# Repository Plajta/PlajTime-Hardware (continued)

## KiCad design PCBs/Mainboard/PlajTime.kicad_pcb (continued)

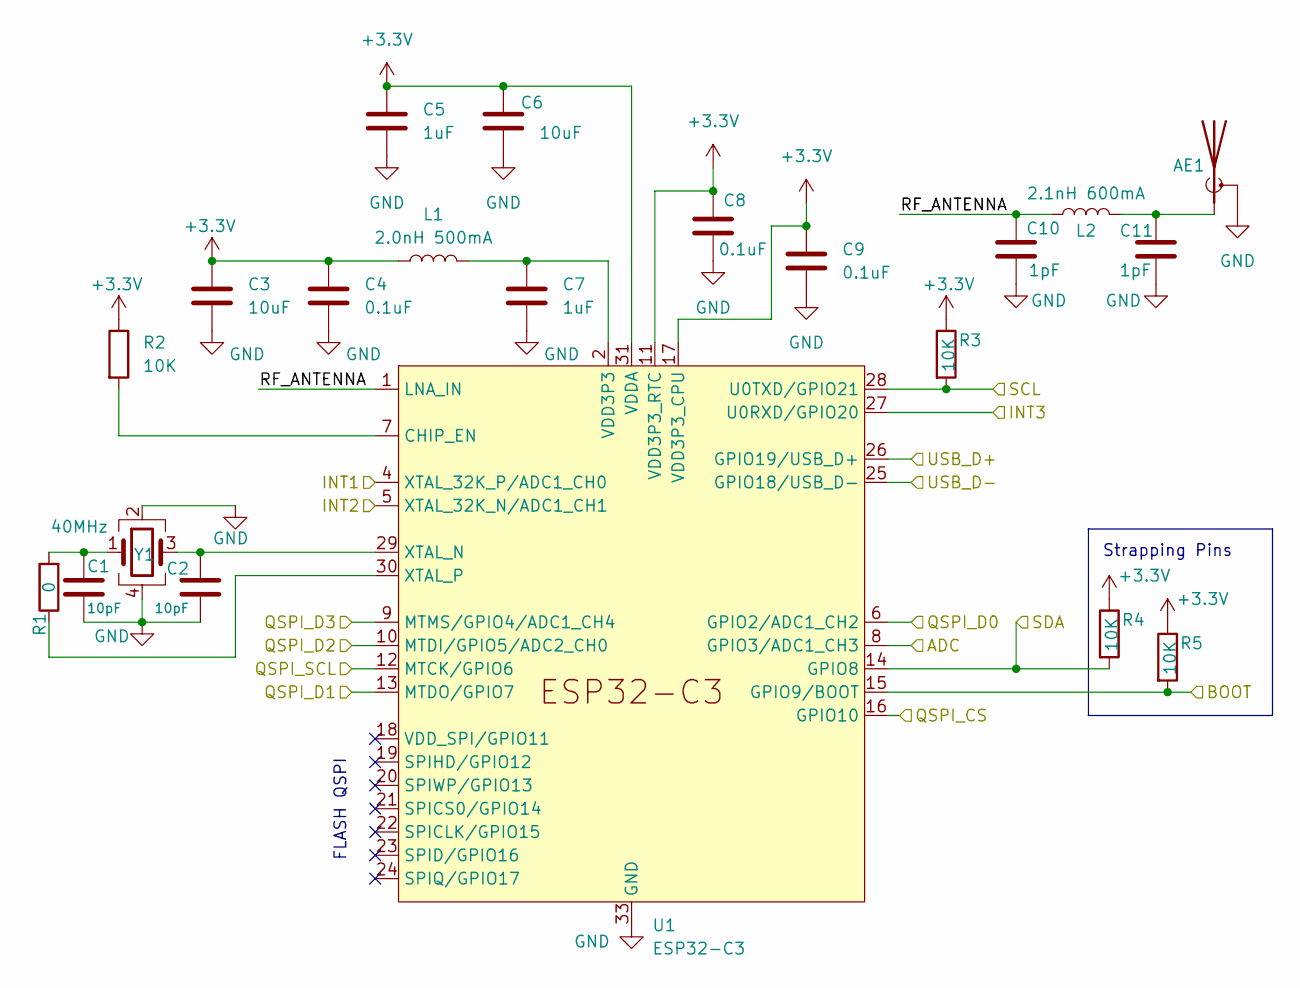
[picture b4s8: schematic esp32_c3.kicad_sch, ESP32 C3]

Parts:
AE1: Antenna_Shield; PinHeader_1x02_P1.00mm_Vertical
C1, C2: 10pF; C_0201_0603Metric
C3, C6: 10uF; C_0402_1005Metric
C4, C8, C9: 0.1uF; C_0201_0603Metric
C5, C7: 1uF; C_0201_0603Metric
C10, C11: 1pF; C_0201_0603Metric
L1: 2.0nH 500mA; L_0201_0603Metric
L2: 2.1nH 600mA; L_0201_0603Metric
R1: 0; R_0201_0603Metric
R2, R3, R4, R5: 10K; R_0201_0603Metric
U1: ESP32-C3; QFN-32-1EP_5x5mm_P0.5mm_EP3.45x3.45mm
Y1: 40MHz; Oscillator_SMD_Abracon_ASCO-4Pin_1.6x1.2mm

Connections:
+3.3V: C3.1, C4.1, C5.1, C6.1, C8.1, C9.1, L1.1, R2.1, R3.1, R4.1, R5.1, U1.11 (VDD3P3_RTC), U1.17 (VDD3P3_CPU), U1.31 (VDDA), U1.32 (VDDA); also elsewhere on the board
/Display/QSPI_CS: U1.16 (GPIO10); also elsewhere on the board
/Display/QSPI_D0: U1.6 (GPIO2/ADC1_CH2); also elsewhere on the board
/Display/QSPI_D1: U1.13 (MTDO/GPIO7); also elsewhere on the board
/Display/QSPI_D2: U1.10 (MTDI/GPIO5/ADC2_CH0); also elsewhere on the board
/Display/QSPI_D3: U1.9 (MTMS/GPIO4/ADC1_CH4); also elsewhere on the board
/Display/QSPI_SCL: U1.12 (MTCK/GPIO6); also elsewhere on the board
/Display/SCL: R3.2, U1.28 (U0TXD/GPIO21); also elsewhere on the board
/Display/SDA: R4.2, U1.14 (GPIO8); also elsewhere on the board
/Display/TE: U1.27 (U0RXD/GPIO20); also elsewhere on the board
/Display/TP_INT: U1.4 (XTAL_32K_P/ADC1_CH0); also elsewhere on the board
/ESP32_C3/ADC: U1.8 (GPIO3/ADC1_CH3); also elsewhere on the board
/ESP32_C3/BOOT: R5.2, U1.15 (GPIO9/BOOT); also elsewhere on the board
/ESP32_C3/INT2: U1.5 (XTAL_32K_N/ADC1_CH1); also elsewhere on the board
/ESP32_C3/RF_ANTENNA: C10.1, L2.1, U1.1 (LNA_IN)
/ESP32_C3/USB_D+: U1.26 (GPIO19/USB_D+); also elsewhere on the board
/ESP32_C3/USB_D-: U1.25 (GPIO18/USB_D-); also elsewhere on the board
GND: AE1.2 (Shield), C1.2, C2.2, C3.2, C4.2, C5.2, C6.2, C7.2, C8.2, C9.2, C10.2, C11.2, U1.33 (GND), Y1.2, Y1.4; also elsewhere on the board
unnamed: AE1.1 (A), C11.1, L2.2
unnamed: C1.1, R1.2, Y1.1
unnamed: C7.1, L1.2, U1.2 (VDD3P3), U1.3 (VDD3P3)
unnamed: R2.2, U1.7 (CHIP_EN)
unnamed: C2.1, U1.29 (XTAL_N), Y1.3
unnamed: R1.1, U1.30 (XTAL_P)

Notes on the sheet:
Strapping Pins
FLASH QSPI

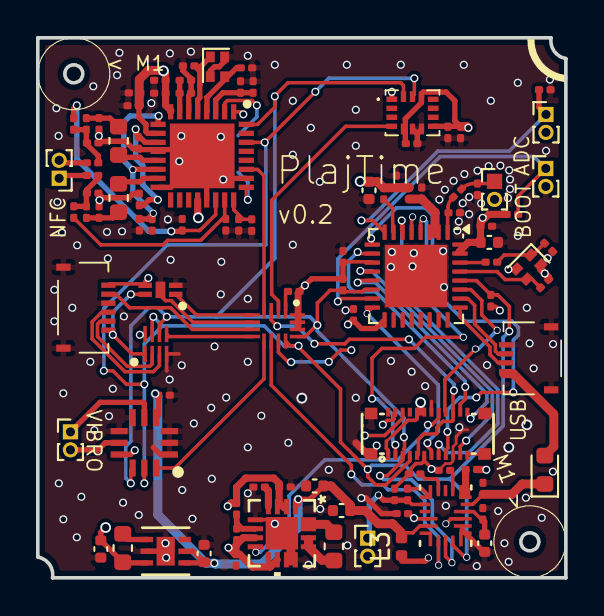
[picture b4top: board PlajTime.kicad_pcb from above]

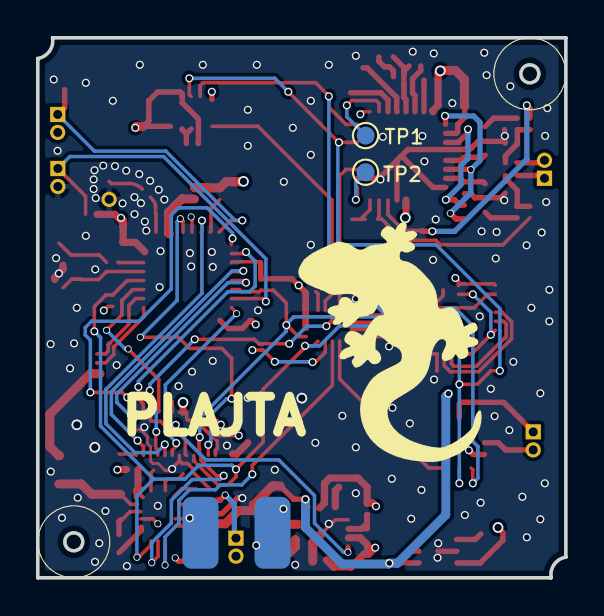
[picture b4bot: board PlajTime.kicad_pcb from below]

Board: 4 copper layers, 29.3 x 30.0 mm, 100 parts (3 on the bottom side), 76 nets.

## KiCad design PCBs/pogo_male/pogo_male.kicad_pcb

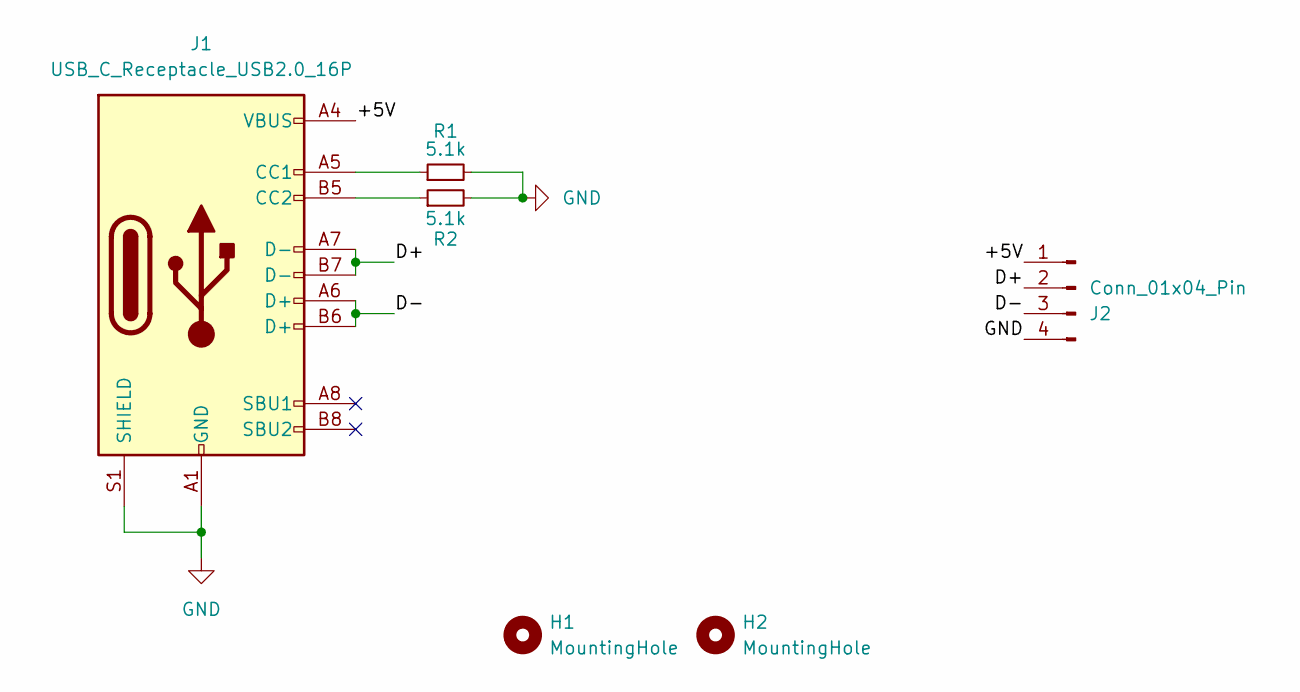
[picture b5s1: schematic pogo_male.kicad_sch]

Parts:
H1, H2: MountingHole; MountingHole_1.2mm_M1
J1: USB_C_Receptacle_USB2.0_16P; USB_C_Receptacle_G-Switch_GT-USB-7010ASV
J2: Conn_01x04_Pin; PinHeader_1x04_P2.54mm_Vertical
R1, R2: 5.1k; R_0402_1005Metric

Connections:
/+5V: J1.A4 (VBUS), J1.A9 (VBUS), J1.B4 (VBUS), J1.B9 (VBUS), J2.1
/D+: J1.A7 (D-), J1.B7 (D-), J2.2
/D-: J1.A6 (D+), J1.B6 (D+), J2.3
GND: J1.A1 (GND), J1.A12 (GND), J1.B1 (GND), J1.B12 (GND), J1.S1 (SHIELD), J2.4, R1.2, R2.2
unnamed: J1.A5 (CC1), R1.1
unnamed: J1.B5 (CC2), R2.1

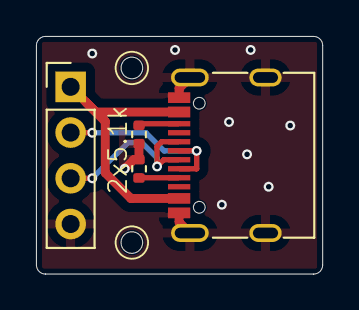
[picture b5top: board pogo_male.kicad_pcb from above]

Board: 2 copper layers, 15.9 x 13.2 mm, 6 parts (0 on the bottom side), 6 nets.

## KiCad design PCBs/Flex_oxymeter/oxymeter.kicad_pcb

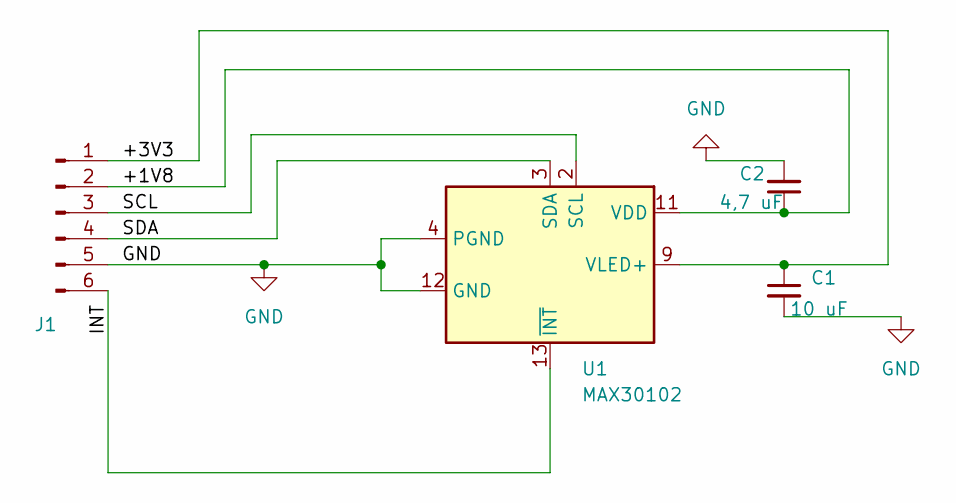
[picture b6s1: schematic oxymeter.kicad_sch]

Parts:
C1: 10 uF; C_0201_0603Metric
C2: 4,7 uF; C_0201_0603Metric
J1: Conn_01x06_Pin; edge_01x06
U1: MAX30102; Maxim_MAX30102

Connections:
/+1V8: C2.1, J1.2, U1.11 (VDD)
/+3V3: C1.1, J1.1, U1.9 (VLED+), U1.10 (VLED+)
/INT: J1.6, U1.13 (~INT)
/SCL: J1.3, U1.2 (SCL)
/SDA: J1.4, U1.3 (SDA)
GND: C1.2, C2.2, J1.5, U1.4 (PGND), U1.12 (GND)

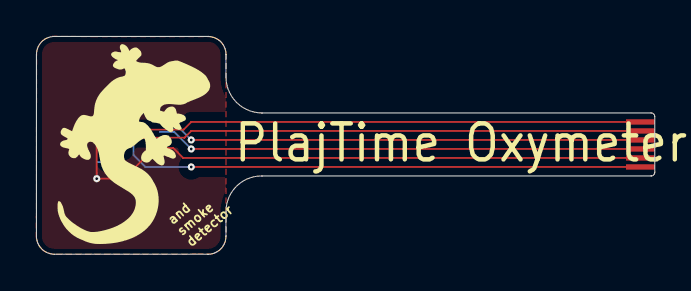
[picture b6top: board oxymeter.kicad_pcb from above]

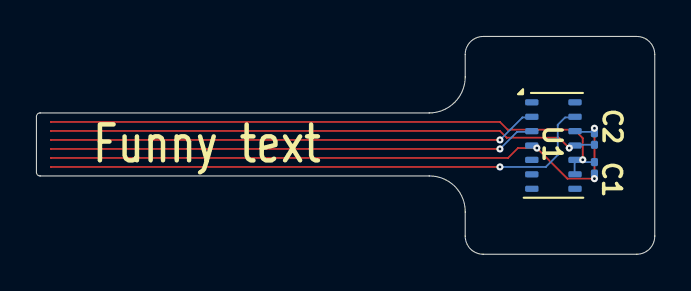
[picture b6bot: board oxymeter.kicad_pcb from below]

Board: 2 copper layers, 34.3 x 12.1 mm, 4 parts (3 on the bottom side), 6 nets.

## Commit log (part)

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2024-08-22 added watch enclosure
2024-08-22 collors yeah nice
2024-08-24 A lot of work has been done! PCB some schematic and 3D
2024-08-29 au bolest
2024-09-02 Some 3d changes
2024-11-22 Reorganize PCB directory Fix .gitignores
2024-11-24 Designed shassis for watch
2024-11-24 added 3mf files to print
2024-12-01 Add Kicad files for Oxymeter flex PCB It is NOT compatible with Mainboard v0.2 since it hasn't yet been updated.
2024-12-01 Add Kicad files for female pogo flex PCB
2024-12-01 Add WIP Kicad files for male pogo PCB
2024-12-02 OHHH Cool shassis and a lot of broken code
2024-12-03 some fixes, touch is a bit faster but a bit laggy
2025-01-07 Fixed vulnerability in 3Ds
2025-01-07 Added more space for display pogo flex pcb and button
2025-01-07 Changed old 3mf to new one
2025-01-09 home is here! brothers
2025-01-10 Cleaning work space
2025-01-15 Added STLs and some minor changes in model
2025-01-17 Minor changes in 3D model
2025-01-30 Update schematic info and add plot in PDF
2025-01-30 Update schematic info and add PDFs for auxiliary boards
2025-02-09 Minor fix in chassis
2025-02-25 Added no turn off display after inactivity
2025-03-05 Added ablity to configure with menuconfig
2025-04-15 Transfered Model to Freecad 1.0.0
2025-04-22 Update the female magnetic Pogopin connector
    Update to KiCAD 9.0
    Add a differential skew to make the differential tracks ACTUALLY the same length (even to it doesn't matter at ESP's speed)
2025-04-24 Fix schematic title
    Also update to KiCAD 9
2025-09-19 Add LICENSE-CC-BY-SA
2025-09-19 Add a README.md
2025-10-30 Squished prototype v0.3 archive
2025-10-30 Clean repo for next prototype
2025-10-30 3D: Add model to show required fitting space
2026-01-26 3D is now has its sizes, PCB has almost done schematic and started work on layout
2026-02-06 Some layout is done
2026-02-08 Final?
2026-02-09 Some small changes
2026-02-09 Add and modify labels
    Modify mainly text thickness
2026-02-09 Move text around a bit
    for future fruity changes
2026-02-09 Add a nice PCB graphic, tweak text
    Add a nice citrus inspired PCB graphic for the bottom side of PlajTime v0.4
2026-02-09 Some small final touches
2026-02-17 Final Main PCB version
2026-03-01 Fixes for bug that I found for now, added right models
2026-03-07 feat: Add new KiCad project for battery flexible PCB, updating main, auxiliary, and 3D models.
2026-03-10 Almost done AUX Board
2026-03-11 Done with battery FPCB
2026-03-11 Add graphics for AUX FPCB
    Redo asset README a bit and move assets
    Remove the pogo pins from the solderpaste layer
2026-03-11 Fix dielectric materials on BAT and AUX
    Add dimensions to BAT and fix it's thickness
2026-03-11 Fix names for AUX graphics
2026-03-11 Update AUX board's top graphic
2026-03-14 Added stiffener for BAT FPCB
2026-03-14 Done with AUX board
2026-03-14 Add graphics for BAT FPCB
    Preapplied to the KiCAD files
2026-03-14 Revise and update FPCB graphics
2026-03-14 Add 3D models for all chips on AUX board
2026-03-14 Changes in 3D model
2026-03-14 Add 3D models for AUX board and connectors
2026-03-15 Fix graphics on both FPCBs
    Change how text is put on paths
    Remove country of origin text
2026-03-15 Update export paths and fills on FPCBs
2026-03-16 Added git ignore for production
2026-03-16 Changed to bigger vias
2026-03-17 Edited via sizes
2026-03-25 All production fixes
2026-04-30 Formal remarks, added usb pins holder to model
